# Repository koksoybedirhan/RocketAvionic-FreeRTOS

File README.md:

This repository contains the hardware and software of the project named "Orta İrtifa Roketler İçin FreeRTOS Tabanlı STM32 İşlemcili Aviyonik Kart Yazılım Tasarımı", which is entitled to be supported by TÜBİTAK 2209-A.

Main Avionic Components:
<br>
STM32F030C8T6, LORA RA-02, L86-M33 GPS, MPU6050, BMP180
<br>

Ground Station Components:
<br>
STM32F030F4P6, LORA RA-02
<br>

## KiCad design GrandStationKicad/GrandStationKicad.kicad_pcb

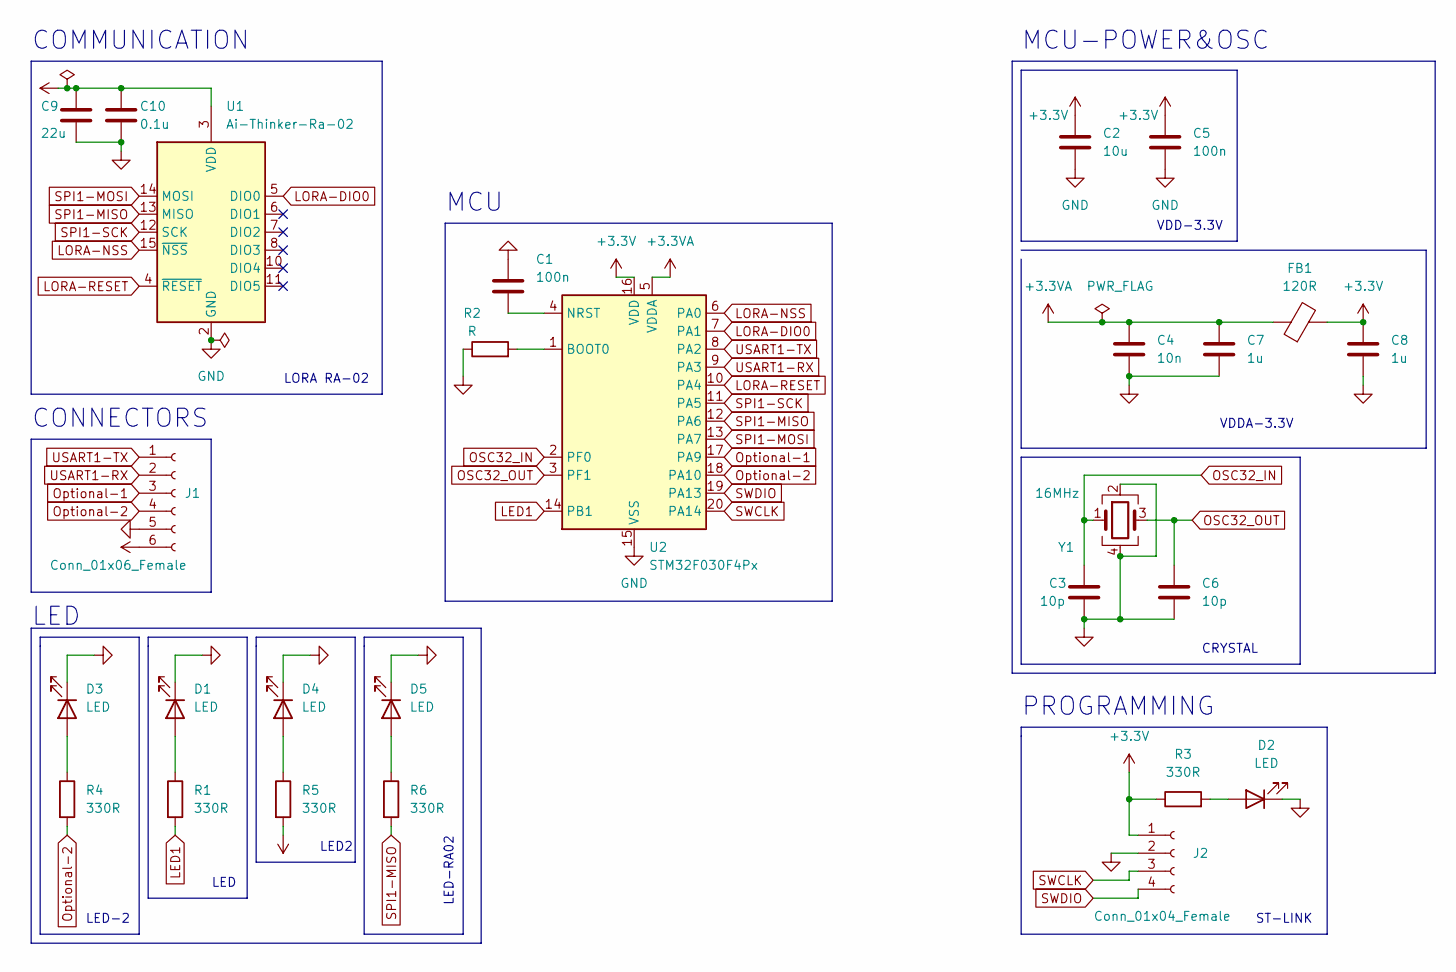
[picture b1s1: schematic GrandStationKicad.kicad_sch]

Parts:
C1: 100n; C_0603_1608Metric
C2: 10u; C_0603_1608Metric
C3, C6: 10p; C_0402_1005Metric
C4: 10n; C_0402_1005Metric
C5: 100n; C_0402_1005Metric
C7, C8: 1u; C_0402_1005Metric
C9: 22u; C_0402_1005Metric
C10: 0.1u; C_0402_1005Metric
D1, D2, D3, D4, D5: LED; LED_0603_1608Metric
FB1: 120R; L_0603_1608Metric
J1: Conn_01x06_Female; PinSocket_1x06_P2.54mm_Vertical
J2: Conn_01x04_Female; PinSocket_1x04_P2.54mm_Vertical
R1, R3, R4, R5, R6: 330R; R_0402_1005Metric
R2: R; R_0402_1005Metric
U1: Ai-Thinker-Ra-02; Ai-Thinker-Ra-01-LoRa
U2: STM32F030F4Px; TSSOP-20_4.4x6.5mm_P0.65mm
Y1: 16MHz; Crystal_SMD_3225-4Pin_3.2x2.5mm

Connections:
+3.3V: C2.1, C5.1, C8.1, C9.1, C10.1, FB1.2, J1.6, J2.1, R3.1, R5.2, U1.3 (VDD), U2.16 (VDD)
+3.3VA: C4.1, C7.1, FB1.1, U2.5 (VDDA)
GND: C1.1, C2.2, C3.2, C4.2, C5.2, C6.2, C7.2, C8.2, C9.2, C10.2, D1.1 (K), D2.1 (K), D3.1 (K), D4.1 (K), D5.1 (K), J1.5, J2.2, R2.1, U1.1 (GND), U1.2 (GND), U1.9 (GND), U1.16 (GND), U2.15 (VSS), Y1.2, Y1.4
LED1: R1.2, U2.14 (PB1)
LORA-DIO0: U1.5 (DIO0), U2.7 (PA1)
LORA-NSS: U1.15 (~NSS), U2.6 (PA0)
LORA-RESET: U1.4 (~RESET), U2.10 (PA4)
unnamed: C1.2, U2.4 (NRST)
unnamed: D1.2 (A), R1.1
unnamed: D2.2 (A), R3.2
unnamed: D3.2 (A), R4.1
unnamed: D4.2 (A), R5.1
unnamed: D5.2 (A), R6.1
unnamed: R2.2, U2.1 (BOOT0)
OSC32_IN: C3.1, U2.2 (PF0), Y1.1
OSC32_OUT: C6.1, U2.3 (PF1), Y1.3
Optional-1: J1.3, U2.17 (PA9)
Optional-2: J1.4, R4.2, U2.18 (PA10)
SPI1-MISO: R6.2, U1.13 (MISO), U2.12 (PA6)
SPI1-MOSI: U1.14 (MOSI), U2.13 (PA7)
SPI1-SCK: U1.12 (SCK), U2.11 (PA5)
SWCLK: J2.3, U2.20 (PA14)
SWDIO: J2.4, U2.19 (PA13)
USART1-RX: J1.2, U2.9 (PA3)
USART1-TX: J1.1, U2.8 (PA2)

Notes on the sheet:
MCU
LED
COMMUNICATION
VDDA-3.3V
PROGRAMMING
LED-RA02
CONNECTORS
LED-2
LED
VDD-3.3V
CRYSTAL
MCU-POWER&OSC
LORA RA-02
LED2
ST-LINK

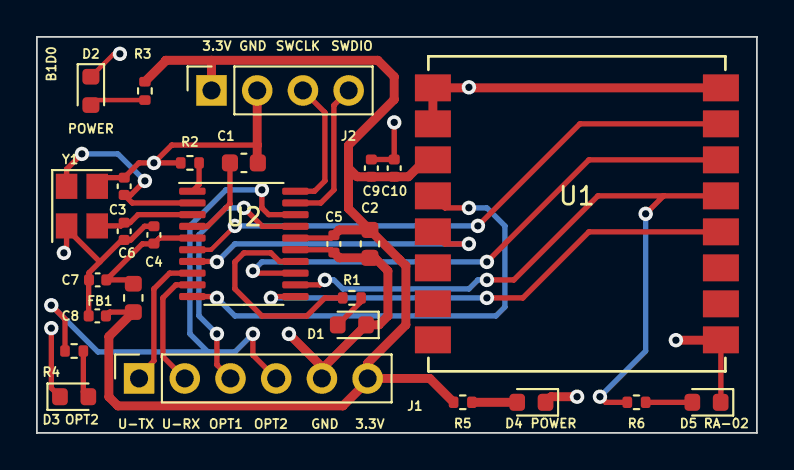
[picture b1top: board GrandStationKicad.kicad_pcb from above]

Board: 2 copper layers, 40.0 x 22.0 mm, 27 parts (0 on the bottom side), 25 nets.

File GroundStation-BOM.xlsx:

Ürün Adı | Birim Fiyatı | Adet | Link
C1, ,"1","100n","C","Capacitor_SMD:C_0603_1608Metric","Unpolarized capacitor","" | 0,16052 ₺ + KDV | 3 | https://ozdisan.com/pasif-komponentler/kapasitorler/smt-smd-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
C2, ,"1","10u","C","Capacitor_SMD:C_0603_1608Metric","Unpolarized capacitor","" | 0,41150 ₺ + KDV | 3 | https://ozdisan.com/pasif-komponentler/kapasitorler/smt-smd-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
C3, C6, ,"2","10p","C","Capacitor_SMD:C_0402_1005Metric","Unpolarized capacitor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 | 0,27797 ₺ + KDV | 6 | https://ozdisan.com/pasif-komponentler/kapasitorler/smt-smd-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
C4, ,"1","10n","C","Capacitor_SMD:C_0402_1005Metric","Unpolarized capacitor","" | 0,10179 ₺ + KDV | 3 | https://ozdisan.com/pasif-komponentler/kapasitorler/smt-smd-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
C5, ,"1","100n","C","Capacitor_SMD:C_0402_1005Metric","Unpolarized capacitor","" | 0,08222 ₺ + KDV | 3 | https://ozdisan.com/pasif-komponentler/kapasitorler/smt-smd-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
C7, C8, ,"2","1u","C","Capacitor_SMD:C_0402_1005Metric","Unpolarized capacitor"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 | 0,15269 ₺ + KDV | 6 | https://ozdisan.com/pasif-komponentler/kapasitorler/smt-smd-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
C9, ,"1","22u","C","Capacitor_SMD:C_0402_1005Metric","Unpolarized capacitor","" | 0,20750 ₺ + KDV | 3 | https://ozdisan.com/pasif-komponentler/kapasitorler/smt-smd-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
C10, ,"1","0.1u","C","Capacitor_SMD:C_0402_1005Metric","Unpolarized capacitor",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 | 0,08222 ₺ + KDV | 3 | https://ozdisan.com/pasif-komponentler/kapasitorler/smt-smd-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
D1, D2, D3, D4, D5, ,"5","LED","LED","LED_SMD:LED_0603_1608Metric","Light emitt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 | 1,08386 ₺ + KDV | 18 | https://ozdisan.com/led-ve-aydinlatma-cozumleri/led-komponen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
FB1, ,"1","120R","FerriteBead","Inductor_SMD:L_0603_1608Metric","Ferrite bead",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 | 0,55479 ₺ + KDV | 3 | https://ozdisan.com/pasif-komponentler/induktorler/bead-feri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
J1, ,"1","Conn_01x06_Female","Conn_01x06_Female","Connector_PinSocket_2.54mm:Pi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 | 2,04647 ₺ + KDV | 3 | https://ozdisan.com/konnektor-ve-baglanti-elemanlari/header-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
J2, ,"1","Conn_01x04_Female","Conn_01x04_Female","Connector_PinSocket_2.54mm:Pi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 | 2,89151 ₺ + KDV | 3 | https://ozdisan.com/konnektor-ve-baglanti-elemanlari/header-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
R1, R3, R4, R5, R6, ,"5","330R","R","Resistor_SMD:R_0402_1005Metric","Resistor"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 | 0,23099 ₺ + KDV | 15 | https://ozdisan.com/pasif-komponentler/direncler/smt-smd-ve-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
R2, ,"1","10K","R","Resistor_SMD:R_0402_1005Metric","Resistor","" | 0,02033 ₺ + KDV | 3 | https://ozdisan.com/pasif-komponentler/direncler/smt-smd-ve-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
U1, ,"1","Ai-Thinker-Ra-02","Ai-Thinker-Ra-02","RF_Module:Ai-Thinker-Ra-01-LoRa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 | 274,95 TL | 2 | https://www.robotistan.com/ra02-lora-modulu-antenli
U2, ,"1","STM32F030F4Px","STM32F030F4Px","Package_SO:TSSOP-20_4.4x6.5mm_P0.65mm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 | 45,20035 ₺ +KDV | 3 | https://ozdisan.com/entegre-devreler-icler/embedded-entegrel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
Y1, ,"1","16MHz","Crystal_GND24","Crystal:Crystal_SMD_3225-4Pin_3.2x2.5mm","Fou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 | 55,54744 ₺ + KDV | 3 | https://ozdisan.com/pasif-komponentler/kristaller-osilatorle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

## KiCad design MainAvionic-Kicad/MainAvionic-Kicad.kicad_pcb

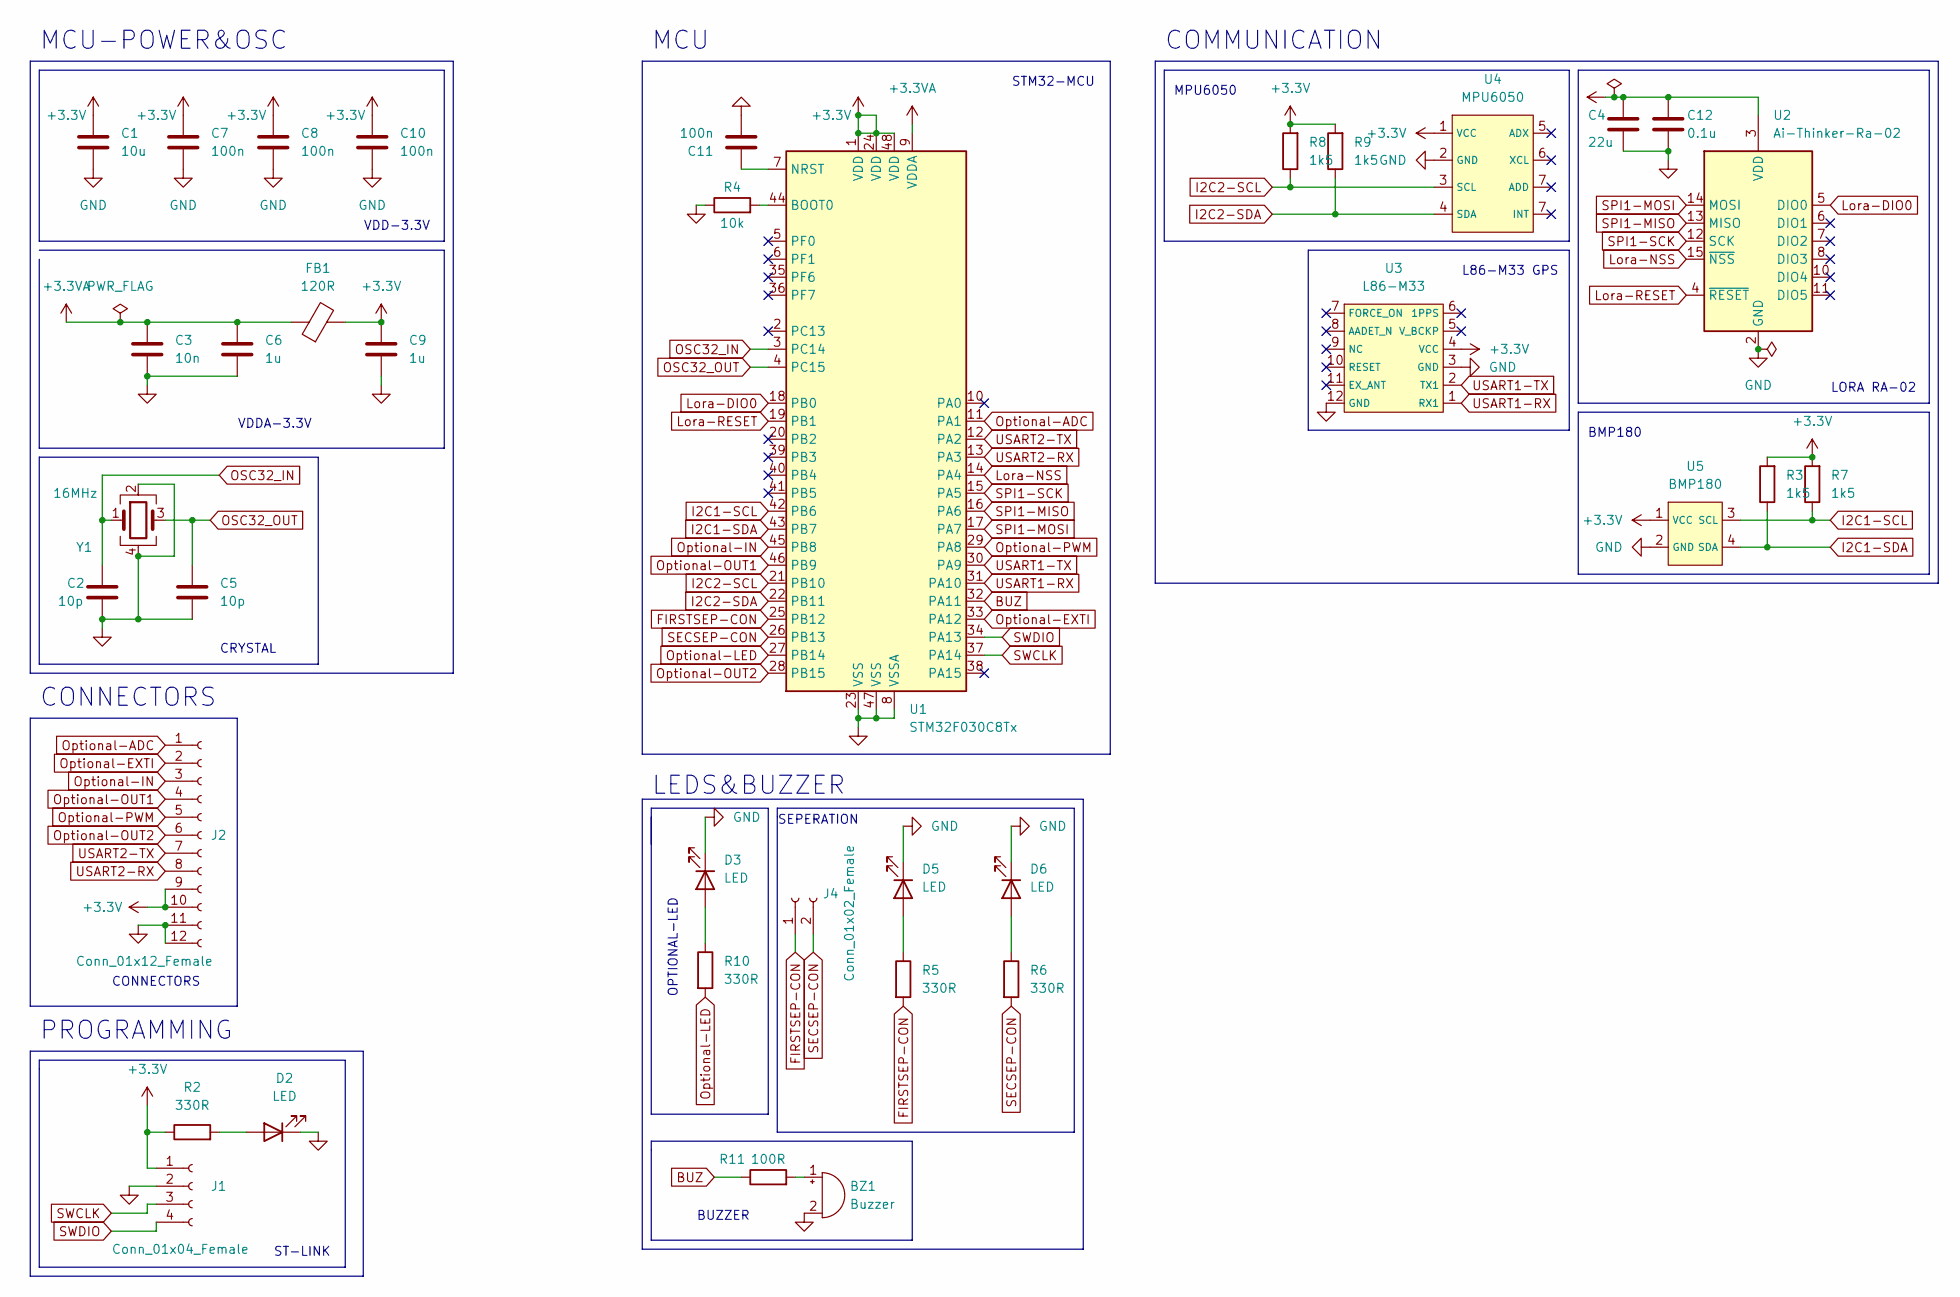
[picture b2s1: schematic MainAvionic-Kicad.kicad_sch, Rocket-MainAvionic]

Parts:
BZ1: Buzzer; Buzzer_15x7.5RM7.6
C1: 10u; C_0603_1608Metric
C2, C5: 10p; C_0402_1005Metric
C3: 10n; C_0402_1005Metric
C4: 22u; C_0402_1005Metric
C6, C9: 1u; C_0402_1005Metric
C7, C8, C10, C11: 100n; C_0402_1005Metric
C12: 0.1u; C_0402_1005Metric
D2, D3, D5, D6: LED; LED_0603_1608Metric
FB1: 120R; L_0603_1608Metric
J1: Conn_01x04_Female; PinSocket_1x04_P2.54mm_Vertical
J2: Conn_01x12_Female; PinSocket_1x12_P2.54mm_Vertical
J4: Conn_01x02_Female; PinSocket_1x02_P2.54mm_Vertical
R2, R5, R6, R10: 330R; R_0402_1005Metric
R3, R7, R8, R9: 1k5; R_0402_1005Metric
R4: 10k; R_0402_1005Metric
R11: 100R; R_0402_1005Metric
U1: STM32F030C8Tx; LQFP-48_7x7mm_P0.5mm
U2: Ai-Thinker-Ra-02; Ai-Thinker-Ra-01-LoRa
U3: L86-M33
U4: MPU6050
U5: BMP180
Y1: 16MHz; Crystal_SMD_3225-4Pin_3.2x2.5mm

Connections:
+3.3V: C1.1, C4.1, C7.1, C8.1, C9.1, C10.1, C12.1, FB1.2, J1.1, J2.9, J2.10, R2.1, R3.2, R7.2, R8.2, R9.2, U1.1 (VDD), U1.24 (VDD), U1.48 (VDD), U2.3 (VDD), U3.4 (VCC), U4.1 (VCC), U5.1 (VCC)
+3.3VA: C3.1, C6.1, FB1.1, U1.9 (VDDA)
BUZ: R11.1, U1.32 (PA11)
FIRSTSEP-CON: J4.1, R5.2, U1.25 (PB12)
GND: BZ1.2 (+), C1.2, C2.2, C3.2, C4.2, C5.2, C6.2, C7.2, C8.2, C9.2, C10.2, C11.2, C12.2, D2.1 (K), D3.1 (K), D5.1 (K), D6.1 (K), J1.2, J2.11, J2.12, R4.1, U1.8 (VSSA), U1.23 (VSS), U1.47 (VSS), U2.1 (GND), U2.2 (GND), U2.9 (GND), U2.16 (GND), U3.3 (GND), U3.12 (GND), U4.2 (GND), U5.2 (GND), Y1.2, Y1.4
I2C1-SCL: R7.1, U1.42 (PB6), U5.3 (SCL)
I2C1-SDA: R3.1, U1.43 (PB7), U5.4 (SDA)
I2C2-SCL: R8.1, U1.21 (PB10), U4.3 (SCL)
I2C2-SDA: R9.1, U1.22 (PB11), U4.4 (SDA)
Lora-DIO0: U1.18 (PB0), U2.5 (DIO0)
Lora-NSS: U1.14 (PA4), U2.15 (~NSS)
Lora-RESET: U1.19 (PB1), U2.4 (~RESET)
unnamed: BZ1.1 (-), R11.2
unnamed: C11.1, U1.7 (NRST)
unnamed: D2.2 (A), R2.2
unnamed: D3.2 (A), R10.1
unnamed: D5.2 (A), R5.1
unnamed: D6.2 (A), R6.1
unnamed: R4.2, U1.44 (BOOT0)
OSC32_IN: C2.1, U1.3 (PC14), Y1.1
OSC32_OUT: C5.1, U1.4 (PC15), Y1.3
Optional-ADC: J2.1, U1.11 (PA1)
Optional-EXTI: J2.2, U1.33 (PA12)
Optional-IN: J2.3, U1.45 (PB8)
Optional-LED: R10.2, U1.27 (PB14)
Optional-OUT1: J2.4, U1.46 (PB9)
Optional-OUT2: J2.6, U1.28 (PB15)
Optional-PWM: J2.5, U1.29 (PA8)
SECSEP-CON: J4.2, R6.2, U1.26 (PB13)
SPI1-MISO: U1.16 (PA6), U2.13 (MISO)
SPI1-MOSI: U1.17 (PA7), U2.14 (MOSI)
SPI1-SCK: U1.15 (PA5), U2.12 (SCK)
SWCLK: J1.3, U1.37 (PA14)
SWDIO: J1.4, U1.34 (PA13)
USART1-RX: U1.31 (PA10), U3.1 (RX1)
USART1-TX: U1.30 (PA9), U3.2 (TX1)
USART2-RX: J2.8, U1.13 (PA3)
USART2-TX: J2.7, U1.12 (PA2)

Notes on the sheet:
VDD-3.3V
STM32-MCU
LEDS&BUZZER
BUZZER
PROGRAMMING
MCU-POWER&OSC
VDDA-3.3V
CONNECTORS
CONNECTORS
COMMUNICATION
CRYSTAL
MCU
ST-LINK
SEPERATION
LORA RA-02
BMP180
MPU6050
L86-M33 GPS
OPTIONAL-LED

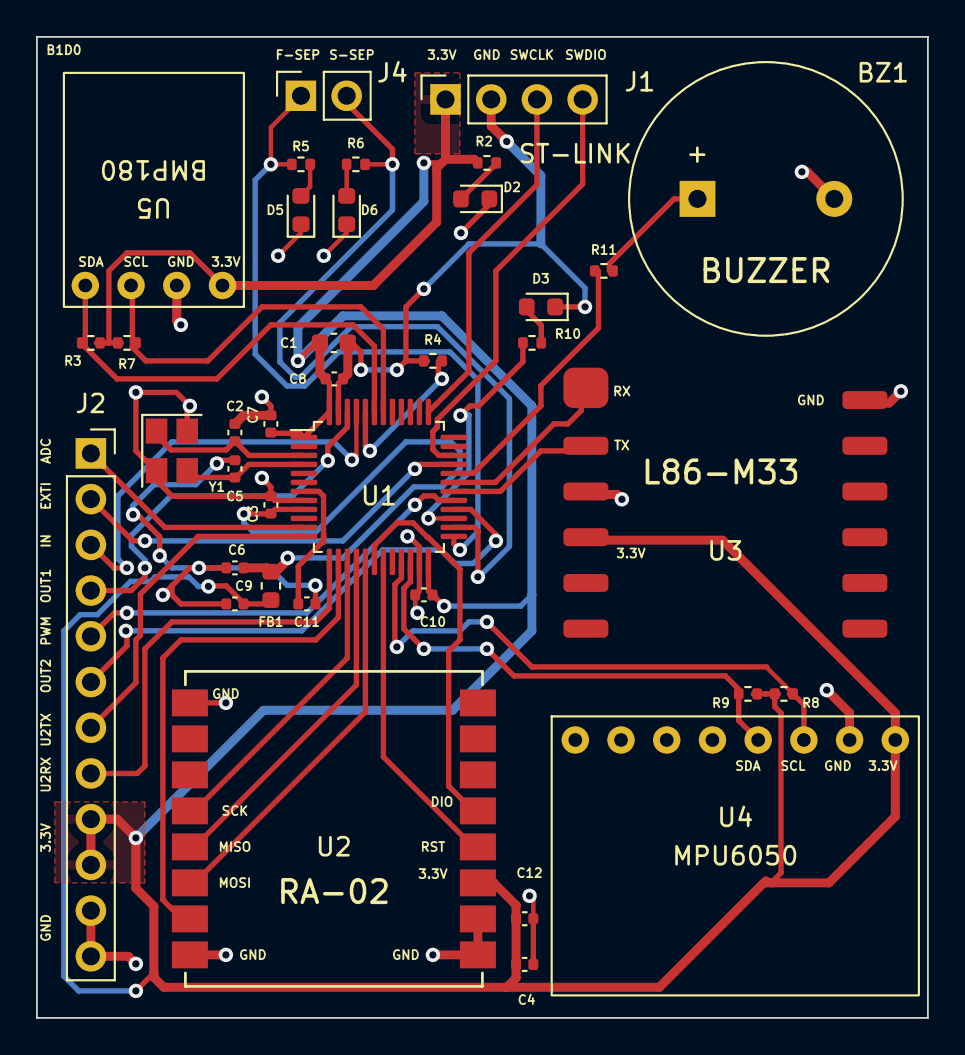
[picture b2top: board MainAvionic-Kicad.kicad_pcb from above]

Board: 2 copper layers, 49.5 x 54.5 mm, 37 parts (0 on the bottom side), 38 nets.

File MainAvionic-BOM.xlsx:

Ürün Adı | Birim Fiyatı | Adet | Link
BZ1, ,"1","Buzzer","Buzzer","Buzzer_Beeper:Buzzer_ 15x7.5RM7.6","Buzzer, polari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 | 12,54210 ₺ + KDV | 3 | https://ozdisan.com/elektromekanik-komponentler/ses-urunleri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
C1, ,"1","10u","C","Capacitor_SMD:C_0603_1608Metric","Unpolarized capacitor","" | 0,41189 ₺ + KDV | 3 | https://ozdisan.com/pasif-komponentler/kapasitorler/smt-smd-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
C2, C5, ,"2","10p","C","Capacitor_SMD:C_0402_1005Metric","Unpolarized capacitor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 | 0,27431 ₺ + KDV | 6 | https://ozdisan.com/pasif-komponentler/kapasitorler/smt-smd-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
C3, ,"1","10n","C","Capacitor_SMD:C_0402_1005Metric","Unpolarized capacitor","" | 0,10189 ₺ + KDV | 3 | https://ozdisan.com/pasif-komponentler/kapasitorler/smt-smd-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
C4, ,"1","22u","C","Capacitor_SMD:C_0402_1005Metric","Unpolarized capacitor","" | 0,20769 ₺ + KDV | 3 | https://ozdisan.com/pasif-komponentler/kapasitorler/smt-smd-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
C6, C9, ,"2","1u","C","Capacitor_SMD:C_0402_1005Metric","Unpolarized capacitor"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 | 0,15283 ₺ + KDV | 6 | https://ozdisan.com/pasif-komponentler/kapasitorler/smt-smd-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
C7, C8, C10, C11, ,"4","100n","C","Capacitor_SMD:C_0402_1005Metric","Unpolarize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 | 0,08229 ₺ + KDV | 12 | https://ozdisan.com/pasif-komponentler/kapasitorler/smt-smd-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
C12, ,"1","0.1u","C","Capacitor_SMD:C_0402_1005Metric","Unpolarized capacitor",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 | 0,08229 ₺ + KDV | 3 | https://ozdisan.com/pasif-komponentler/kapasitorler/smt-smd-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
D2, D3, D5, D6, ,"4","LED","LED","LED_SMD:LED_0603_1608Metric","Light emitting 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 | 1,08386 ₺ + KDV | 4 | https://ozdisan.com/led-ve-aydinlatma-cozumleri/led-komponen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
FB1, ,"1","120R","FerriteBead","Inductor_SMD:L_0603_1608Metric","Ferrite bead",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 | 0,55479 ₺ + KDV | 3 | https://ozdisan.com/pasif-komponentler/induktorler/bead-feri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
J1, ,"1","Conn_01x04_Female","Conn_01x04_Female","Connector_PinSocket_2.54mm:Pi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 | 2,89151 ₺ + KDV | 3 | https://ozdisan.com/konnektor-ve-baglanti-elemanlari/header-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
J2, ,"1","Conn_01x12_Female","Conn_01x12_Female","Connector_PinSocket_2.54mm:Pi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 | 7,67155 ₺ + KDV | 3 | https://ozdisan.com/konnektor-ve-baglanti-elemanlari/header-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
J4, ,"1","Conn_01x02_Female","Conn_01x02_Female","Connector_PinSocket_2.54mm:Pi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 | 1,57033 ₺ + KDV | 3 | https://ozdisan.com/konnektor-ve-baglanti-elemanlari/header-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
R2, R5, R6, R10, ,"4","330R","R","Resistor_SMD:R_0402_1005Metric","Resistor","" | 0,23099 ₺ + KDV | 12 | https://ozdisan.com/pasif-komponentler/direncler/smt-smd-ve-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
R3, R7, R8, R9, ,"4","1k5","R","Resistor_SMD:R_0402_1005Metric","Resistor","" | 0,05878 ₺ + KDV | 12 | https://ozdisan.com/pasif-komponentler/direncler/smt-smd-ve-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
R4, ,"1","10k","R","Resistor_SMD:R_0402_1005Metric","Resistor","" | 0,02033 ₺ + KDV | 3 | https://ozdisan.com/pasif-komponentler/direncler/smt-smd-ve-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
R11, ,"1","100R","R","Resistor_SMD:R_0402_1005Metric","Resistor","" | 0,02035 ₺ + KDV | 3 | https://ozdisan.com/pasif-komponentler/direncler/smt-smd-ve-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
U1, ,"1","STM32F030C8Tx","STM32F030C8Tx","Package_QFP:LQFP-48_7x7mm_P0.5mm","AR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 | 102,93099 ₺ + KDV | 3 | https://ozdisan.com/entegre-devreler-icler/embedded-entegrel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
U2, ,"1","Ai-Thinker-Ra-02","Ai-Thinker-Ra-02","RF_Module:Ai-Thinker-Ra-01-LoRa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 | 274,95 TL | 4 | https://www.robotistan.com/ra02-lora-modulu-antenli
U3, ,"1","L86-M33","L86-M33","F030C8T6:L86-M33","","" | 361,19 TL | 3 | https://www.empastore.com/l86-m33?gad_source=1&gclid=CjwKCAi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
U4, ,"1","MPU6050","MPU6050","F030C8T6:MPU6050","","" | 77,72 TL | 3 | https://www.robotistan.com/mpu6050-6-eksen-ivme-ve-gyro-sens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
U5, ,"1","BMP180","BMP180","F030C8T6:BMP180","","" | 24,45 TL | 3 | https://www.direnc.net/bmp180-dijital-barometrik-sensor
Y1, ,"1","16MHz","Crystal_GND24","Crystal:Crystal_SMD_3225-4Pin_3.2x2.5mm","Fou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 | 55,54744 ₺ + KDV | 3 | https://ozdisan.com/pasif-komponentler/kristaller-osilatorle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

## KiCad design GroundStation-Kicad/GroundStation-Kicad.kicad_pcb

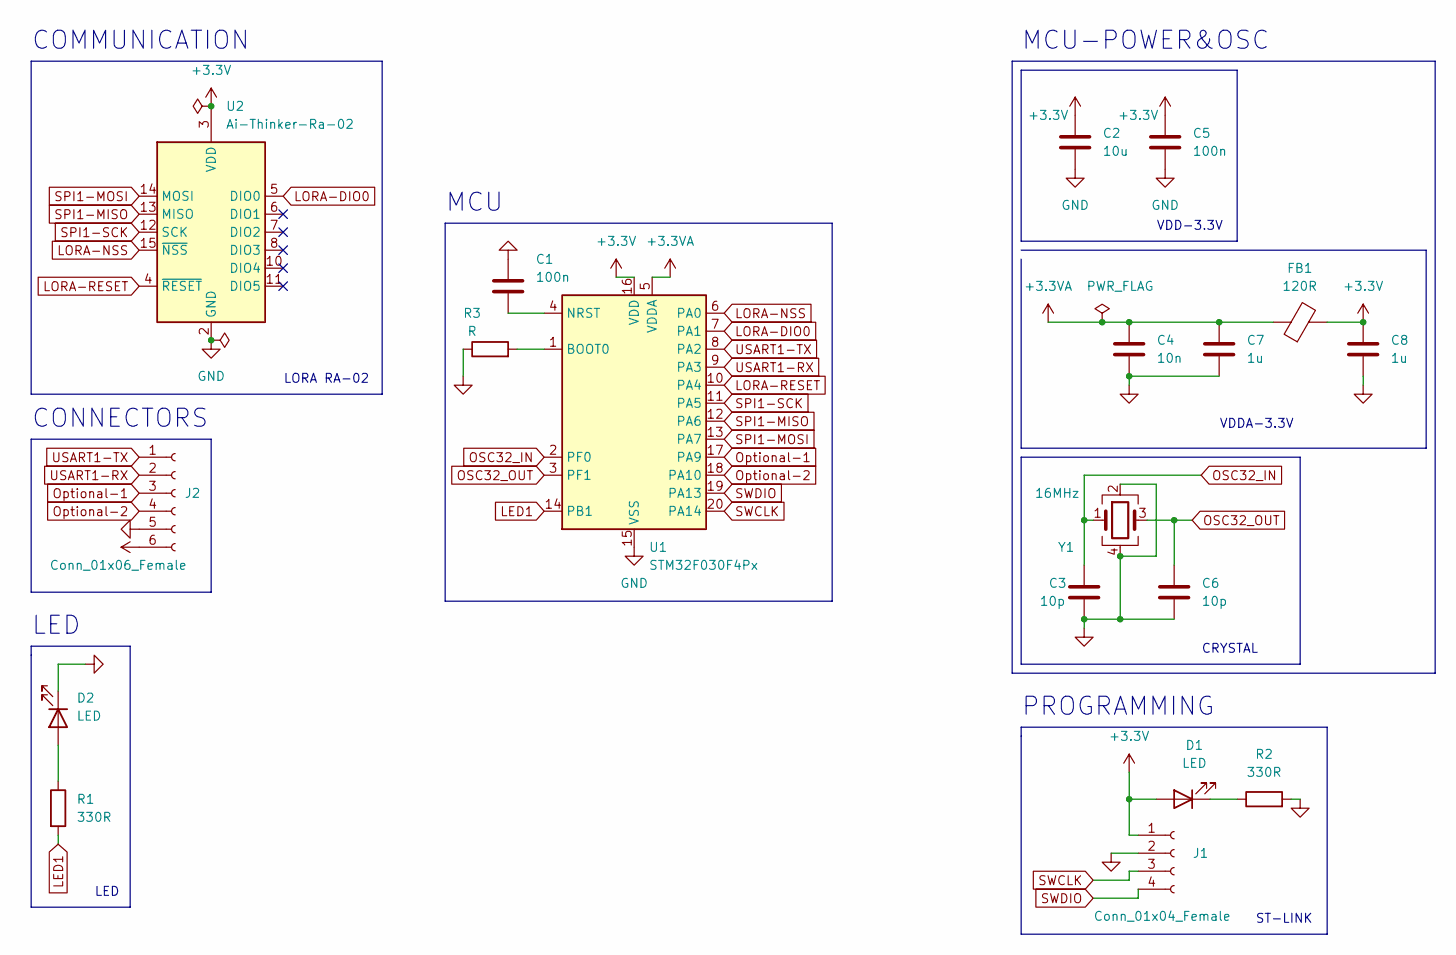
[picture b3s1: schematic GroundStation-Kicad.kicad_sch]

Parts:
C1: 100n; C_0603_1608Metric
C2: 10u; C_0603_1608Metric
C3, C6: 10p; C_0402_1005Metric
C4: 10n; C_0402_1005Metric
C5: 100n; C_0402_1005Metric
C7, C8: 1u; C_0402_1005Metric
D1, D2: LED; LED_0603_1608Metric
FB1: 120R; L_0603_1608Metric
J1: Conn_01x04_Female; PinSocket_1x04_P2.54mm_Vertical
J2: Conn_01x06_Female; PinSocket_1x06_P2.54mm_Vertical
R1, R2: 330R; R_0402_1005Metric
R3: R; R_0402_1005Metric
U1: STM32F030F4Px; TSSOP-20_4.4x6.5mm_P0.65mm
U2: Ai-Thinker-Ra-02; Ai-Thinker-Ra-01-LoRa
Y1: 16MHz; Crystal_SMD_3225-4Pin_3.2x2.5mm

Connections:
+3.3V: C2.1, C5.1, C8.1, D1.2 (A), FB1.2, J1.1, J2.6, U1.16 (VDD), U2.3 (VDD)
+3.3VA: C4.1, C7.1, FB1.1, U1.5 (VDDA)
GND: C1.1, C2.2, C3.2, C4.2, C5.2, C6.2, C7.2, C8.2, D2.1 (K), J1.2, J2.5, R2.2, R3.1, U1.15 (VSS), U2.1 (GND), U2.2 (GND), U2.9 (GND), U2.16 (GND), Y1.2, Y1.4
LED1: R1.2, U1.14 (PB1)
LORA-DIO0: U1.7 (PA1), U2.5 (DIO0)
LORA-NSS: U1.6 (PA0), U2.15 (~NSS)
LORA-RESET: U1.10 (PA4), U2.4 (~RESET)
unnamed: C1.2, U1.4 (NRST)
unnamed: D1.1 (K), R2.1
unnamed: D2.2 (A), R1.1
unnamed: R3.2, U1.1 (BOOT0)
OSC32_IN: C3.1, U1.2 (PF0), Y1.1
OSC32_OUT: C6.1, U1.3 (PF1), Y1.3
Optional-1: J2.3, U1.17 (PA9)
Optional-2: J2.4, U1.18 (PA10)
SPI1-MISO: U1.12 (PA6), U2.13 (MISO)
SPI1-MOSI: U1.13 (PA7), U2.14 (MOSI)
SPI1-SCK: U1.11 (PA5), U2.12 (SCK)
SWCLK: J1.3, U1.20 (PA14)
SWDIO: J1.4, U1.19 (PA13)
USART1-RX: J2.2, U1.9 (PA3)
USART1-TX: J2.1, U1.8 (PA2)

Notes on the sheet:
PROGRAMMING
MCU
ST-LINK
COMMUNICATION
VDD-3.3V
LORA RA-02
LED
CRYSTAL
LED
CONNECTORS
MCU-POWER&OSC
VDDA-3.3V

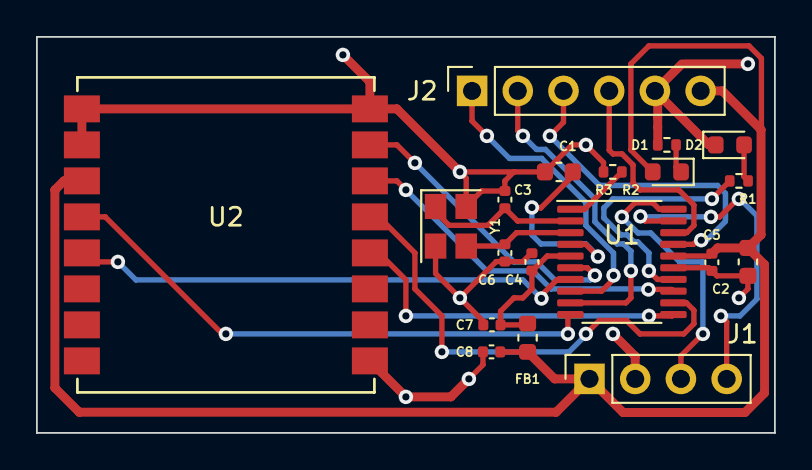
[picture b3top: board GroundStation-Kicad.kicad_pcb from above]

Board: 2 copper layers, 41.0 x 22.0 mm, 19 parts (0 on the bottom side), 22 nets.

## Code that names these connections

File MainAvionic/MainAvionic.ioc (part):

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Mcu.Name=STM32F030C8Tx
Mcu.Package=LQFP48
Mcu.UserName=STM32F030C8Tx
PA0.Mode=SYS_WakeUp0
PA0.Signal=SYS_WKUP1
PA1.GPIOParameters=GPIO_Label
PA1.GPIO_Label=Optional-ADC
PA1.Mode=IN1
PA1.Signal=ADC_IN1
PA10.Mode=Asynchronous
PA10.Signal=USART1_RX
PA11.GPIOParameters=GPIO_Label
PA11.GPIO_Label=BUZZER
PA11.Signal=GPIO_Output
PA12.GPIOParameters=GPIO_Label
PA12.GPIO_Label=Optional-EXTI
PA12.Signal=GPXTI12
PA13.Mode=Serial_Wire
PA13.Signal=SYS_SWDIO
PA14.Mode=Serial_Wire
PA14.Signal=SYS_SWCLK
PA2.Mode=Asynchronous
PA2.Signal=USART2_TX
PA3.Mode=Asynchronous
PA3.Signal=USART2_RX
PA4.GPIOParameters=GPIO_Label
PA4.GPIO_Label=Lora-NSS
PA4.Signal=GPIO_Output
PA5.Mode=Full_Duplex_Master
PA5.Signal=SPI1_SCK
PA6.Mode=Full_Duplex_Master
PA6.Signal=SPI1_MISO
PA7.Mode=Full_Duplex_Master
PA7.Signal=SPI1_MOSI
PA8.GPIOParameters=GPIO_Label
PA8.GPIO_Label=Optional-PWM
PA8.Signal=S_TIM1_CH1
PA9.Mode=Asynchronous
PA9.Signal=USART1_TX
PB0.GPIOParameters=GPIO_Label
PB0.GPIO_Label=Lora-DIO0
PB0.Signal=GPIO_Input
PB1.GPIOParameters=GPIO_Label
PB1.GPIO_Label=Lora-RESET
PB1.Signal=GPIO_Output
PB10.Mode=I2C
PB10.Signal=I2C2_SCL
PB11.Mode=I2C
PB11.Signal=I2C2_SDA
PB12.GPIOParameters=GPIO_Label
PB12.GPIO_Label=First-Seperation
PB12.Signal=GPIO_Output
PB13.GPIOParameters=GPIO_Label
PB13.GPIO_Label=Second-Seperation
PB13.Signal=GPIO_Output
PB14.GPIOParameters=GPIO_Label
PB14.GPIO_Label=Optional-LED
PB14.Signal=GPIO_Output
PB15.GPIOParameters=GPIO_Label
PB15.GPIO_Label=Optional-OUT2
PB15.Signal=GPIO_Output
PB4.GPIOParameters=GPIO_Label
PB4.GPIO_Label=SECSEP-LED
PB4.Signal=GPIO_Output
PB5.GPIOParameters=GPIO_Label
PB5.GPIO_Label=FIRSTSEP-LED
PB5.Signal=GPIO_Output
PB6.Mode=I2C
PB6.Signal=I2C1_SCL
PB7.Mode=I2C
PB7.Signal=I2C1_SDA
PB8.GPIOParameters=GPIO_Label
PB8.GPIO_Label=Optional-IN
PB8.Signal=GPIO_Input
PB9.GPIOParameters=GPIO_Label
PB9.GPIO_Label=Optional-OUT
PB9.Signal=GPIO_Output
PC14-OSC32_IN.Mode=LSE-External-Oscillator
PC14-OSC32_IN.Signal=RCC_OSC32_IN
PC15-OSC32_OUT.Mode=LSE-External-Oscillator
PC15-OSC32_OUT.Signal=RCC_OSC32_OUT
RCC.SYSCLKFreq_VALUE=32000000
RCC.SYSCLKSource=RCC_SYSCLKSOURCE_PLLCLK
board=custom

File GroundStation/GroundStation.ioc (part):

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Mcu.Name=STM32F030F4Px
Mcu.Package=TSSOP20
Mcu.UserName=STM32F030F4Px
PA0.GPIOParameters=GPIO_Label
PA0.GPIO_Label=LORA-NSS
PA0.Signal=GPIO_Output
PA1.GPIOParameters=GPIO_Label
PA1.GPIO_Label=LORA-DIO0
PA1.Signal=GPIO_Input
PA10.GPIOParameters=GPIO_Label
PA10.GPIO_Label=Optional-2
PA10.Signal=GPIO_Output
PA13.Mode=Serial_Wire
PA13.Signal=SYS_SWDIO
PA14.Mode=Serial_Wire
PA14.Signal=SYS_SWCLK
PA2.Mode=Asynchronous
PA2.Signal=USART1_TX
PA3.Mode=Asynchronous
PA3.Signal=USART1_RX
PA4.GPIOParameters=GPIO_Label
PA4.GPIO_Label=LORA-RESET
PA4.Signal=GPIO_Output
PA5.Mode=Full_Duplex_Master
PA5.Signal=SPI1_SCK
PA6.Mode=Full_Duplex_Master
PA6.Signal=SPI1_MISO
PA7.Mode=Full_Duplex_Master
PA7.Signal=SPI1_MOSI
PA9.GPIOParameters=GPIO_Label
PA9.GPIO_Label=Optional-1
PA9.Signal=GPIO_Output
PB1.GPIOParameters=GPIO_Label
PB1.GPIO_Label=LED
PB1.Signal=GPIO_Output
PF0-OSC_IN.Mode=HSE-External-Oscillator
PF0-OSC_IN.Signal=RCC_OSC_IN
PF1-OSC_OUT.Mode=HSE-External-Oscillator
PF1-OSC_OUT.Signal=RCC_OSC_OUT
RCC.SYSCLKFreq_VALUE=48000000
RCC.SYSCLKSource=RCC_SYSCLKSOURCE_PLLCLK
board=custom

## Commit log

2023-11-19 first
2023-11-19 upd20-11-23
2023-11-24 update251123
2023-11-25 update25-11-23
2023-11-26 update271123
2023-11-28 29-11-23
2023-12-01 1-12-23
2023-12-02 update2-12-23
2023-12-03 update3-12-23
2023-12-03 update4-12-23
2023-12-05 update5-12-23
2023-12-08 update9-12-23
2023-12-22 update23-12-23
2024-01-16 update16-01-24
2024-02-18 update18-02-24
2024-02-19 update19-02-24
2024-02-19 update20-02-24
2024-02-20 update21-02-24
2024-02-21 update-22-02-24
